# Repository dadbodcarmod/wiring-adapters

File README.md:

DadBodCarMod Wiring Adapters
============================

Wiring adapters for the various cars we modify.

While we sometimes do custom wiring, one of the goals of our projects is to
simplify these projects so the average "dad bod" can do these to their own cars.
These adapters are ones we've created to minimize the required wiring changes to
our stock-ish cars.

Corolla 2006 DBW Dash to ADU
----------------------------

This adapter is for connecting an ECU Masters Advanced Display Unit (ADU) to the
stock dash connector on a Toyota Corolla.  This will likely work on other models
that have a similar dash.  It's intended to be used with a car using the ECU
Masters EMU Black engine computer, so many of the stock light/functions aren't
connected (e.g. tachometer comes via CAN bus instead of stock pin).

 * For EMU Master Advanced Display Unit (ADU)
 * For use with ECU Master EMU Black (likely will work with EMU Classic)
 * For use on Toyota Corolla 2003 to 2006 (tested on 2003 and 2006)
 * For use on Drive-by-Wire (DBW) and non-DBW cars
 * For use on cars without Anti-lock Braking System (ABS); two or three changes
   required for ABS

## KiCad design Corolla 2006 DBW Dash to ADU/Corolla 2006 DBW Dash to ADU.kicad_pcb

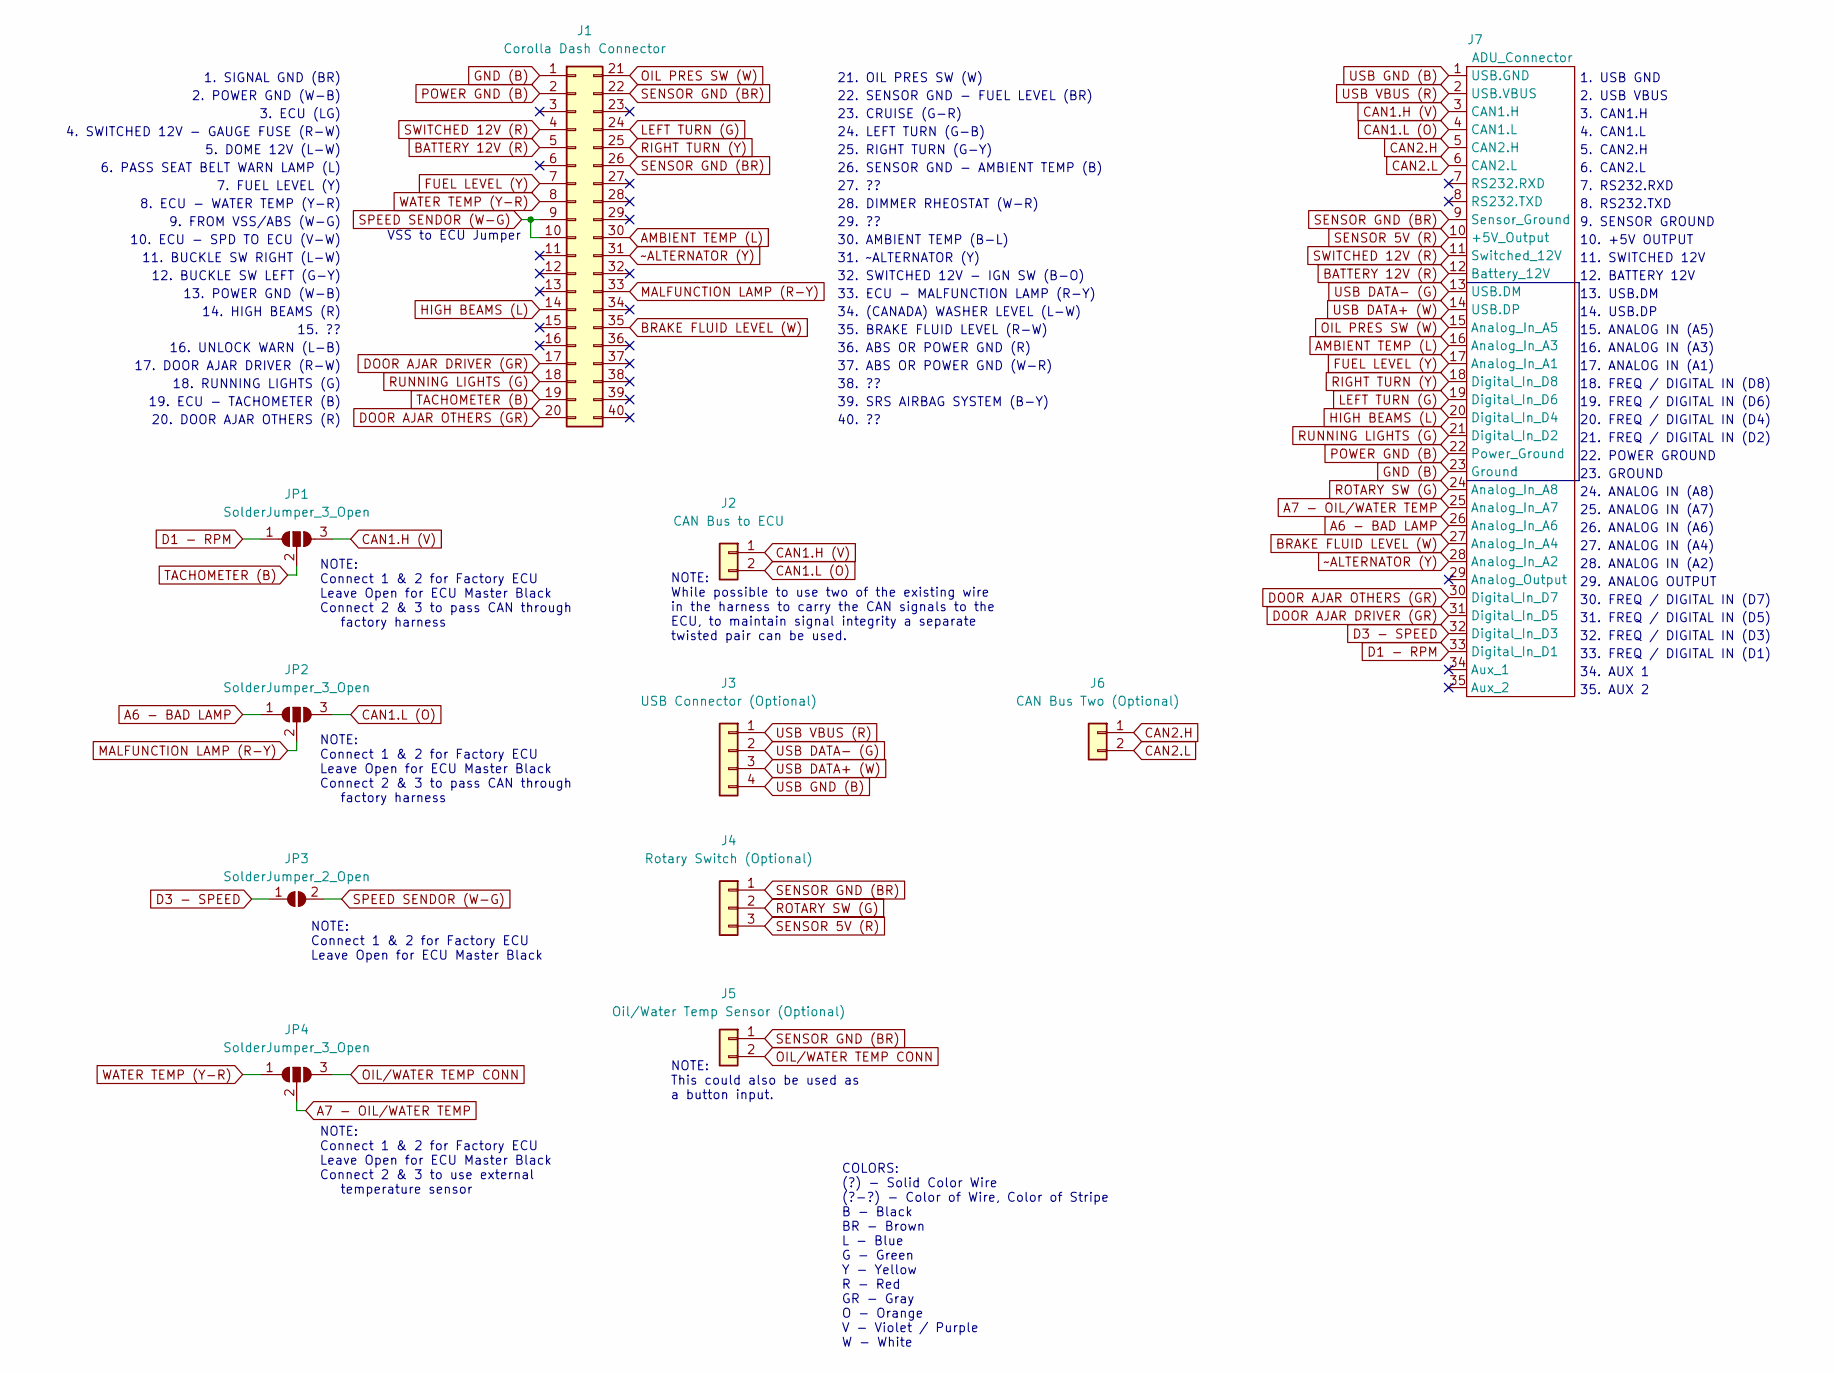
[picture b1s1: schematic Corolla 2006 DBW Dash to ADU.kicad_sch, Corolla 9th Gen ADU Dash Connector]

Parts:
J1: Corolla Dash Connector; 2006 Corolla Dash Connector
J2: CAN Bus to ECU; SolderWire-0.75sqmm_1x02_P4.8mm_D1.25mm_OD2.3mm_Relief
J3: USB Connector (Optional); SolderWire-0.25sqmm_1x04_P4.2mm_D0.65mm_OD1.7mm_Relief
J4: Rotary Switch (Optional); SolderWire-0.75sqmm_1x03_P4.8mm_D1.25mm_OD2.3mm_Relief
J5: Oil/Water Temp Sensor (Optional); SolderWire-0.75sqmm_1x02_P4.8mm_D1.25mm_OD2.3mm_Relief
J6: CAN Bus Two (Optional); SolderWire-0.75sqmm_1x02_P4.8mm_D1.25mm_OD2.3mm_Relief
J7: ADU_Connector; Wires for ADU Connector
JP1, JP2, JP4: SolderJumper_3_Open; SolderJumper-3_P1.3mm_Open_RoundedPad1.0x1.5mm_NumberLabels
JP3: SolderJumper_2_Open; SolderJumper-2_P1.3mm_Open_RoundedPad1.0x1.5mm

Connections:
A6 - BAD LAMP: J7.26 (Analog_In_A6), JP2.1 (A)
A7 - OIL/WATER TEMP: J7.25 (Analog_In_A7), JP4.2 (C)
AMBIENT TEMP (L): J1.30, J7.16 (Analog_In_A3)
BATTERY 12V (R): J1.5, J7.12 (Battery_12V)
BRAKE FLUID LEVEL (W): J1.35, J7.27 (Analog_In_A4)
CAN1.H (V): J2.1, J7.3 (CAN1.H), JP1.3 (B)
CAN1.L (O): J2.2, J7.4 (CAN1.L), JP2.3 (B)
CAN2.H: J6.1, J7.5 (CAN2.H)
CAN2.L: J6.2, J7.6 (CAN2.L)
D1 - RPM: J7.33 (Digital_In_D1), JP1.1 (A)
D3 - SPEED: J7.32 (Digital_In_D3), JP3.1 (A)
DOOR AJAR DRIVER (GR): J1.17, J7.31 (Digital_In_D5)
DOOR AJAR OTHERS (GR): J1.20, J7.30 (Digital_In_D7)
FUEL LEVEL (Y): J1.7, J7.17 (Analog_In_A1)
GND (B): J1.1, J7.23 (Ground)
HIGH BEAMS (L): J1.14, J7.20 (Digital_In_D4)
LEFT TURN (G): J1.24, J7.19 (Digital_In_D6)
MALFUNCTION LAMP (R-Y): J1.33, JP2.2 (C)
OIL PRES SW (W): J1.21, J7.15 (Analog_In_A5)
OIL/WATER TEMP CONN: J5.2, JP4.3 (B)
POWER GND (B): J1.2, J7.22 (Power_Ground)
RIGHT TURN (Y): J1.25, J7.18 (Digital_In_D8)
ROTARY SW (G): J4.2, J7.24 (Analog_In_A8)
RUNNING LIGHTS (G): J1.18, J7.21 (Digital_In_D2)
SENSOR 5V (R): J4.3, J7.10 (+5V_Output)
SENSOR GND (BR): J1.22, J1.26, J4.1, J5.1, J7.9 (Sensor_Ground)
SPEED SENDOR (W-G): J1.9, J1.10, JP3.2 (B)
SWITCHED 12V (R): J1.4, J7.11 (Switched_12V)
TACHOMETER (B): J1.19, JP1.2 (C)
USB DATA+ (W): J3.3, J7.14 (USB.DP)
USB DATA- (G): J3.2, J7.13 (USB.DM)
USB GND (B): J3.4, J7.1 (USB.GND)
USB VBUS (R): J3.1, J7.2 (USB.VBUS)
WATER TEMP (Y-R): J1.8, JP4.1 (A)
~ALTERNATOR (Y): J1.31, J7.28 (Analog_In_A2)

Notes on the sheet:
2. POWER GND (W-B)
38. ??
2. USB VBUS
14. USB.DP
34. (CANADA) WASHER LEVEL (L-W)
27. ANALOG IN (A4)
5. DOME 12V (L-W)
12. BUCKLE SW LEFT (G-Y)
8. RS232.TXD
4. SWITCHED 12V - GAUGE FUSE (R-W)
35. BRAKE FLUID LEVEL (R-W)
20. DOOR AJAR OTHERS (R)
33. ECU - MALFUNCTION LAMP (R-Y)
9. FROM VSS/ABS (W-G)
21. OIL PRES SW (W)
6. PASS SEAT BELT WARN LAMP (L)
20. FREQ / DIGITAL IN (D4)
3. ECU (LG)
18. RUNNING LIGHTS (G)
NOTE: Connect 1 & 2 for Factory ECU Leave Open for ECU Master Black Connect 2 & 3 to pass CAN through factory harness
31. ~ALTERNATOR (Y)
17. DOOR AJAR DRIVER (R-W)
3. CAN1.H
19. FREQ / DIGITAL IN (D6)
5. CAN2.H
18. FREQ / DIGITAL IN (D8)
33. FREQ / DIGITAL IN (D1)
4. CAN1.L
25. ANALOG IN (A7)
34. AUX 1
31. FREQ / DIGITAL IN (D5)
13. POWER GND (W-B)
COLORS: (?) - Solid Color Wire (?-?) - Color of Wire, Color of Stripe B - Black BR - Brown L - Blue G - Green Y - Yellow R - Red GR - Gray O - Orange V - Violet / Purple W - White
17. ANALOG IN (A1)
21. FREQ / DIGITAL IN (D2)
40. ??
23. CRUISE (G-R)
30. FREQ / DIGITAL IN (D7)
12. BATTERY 12V
NOTE: Connect 1 & 2 for Factory ECU Leave Open for ECU Master Black Connect 2 & 3 to use external temperature sensor

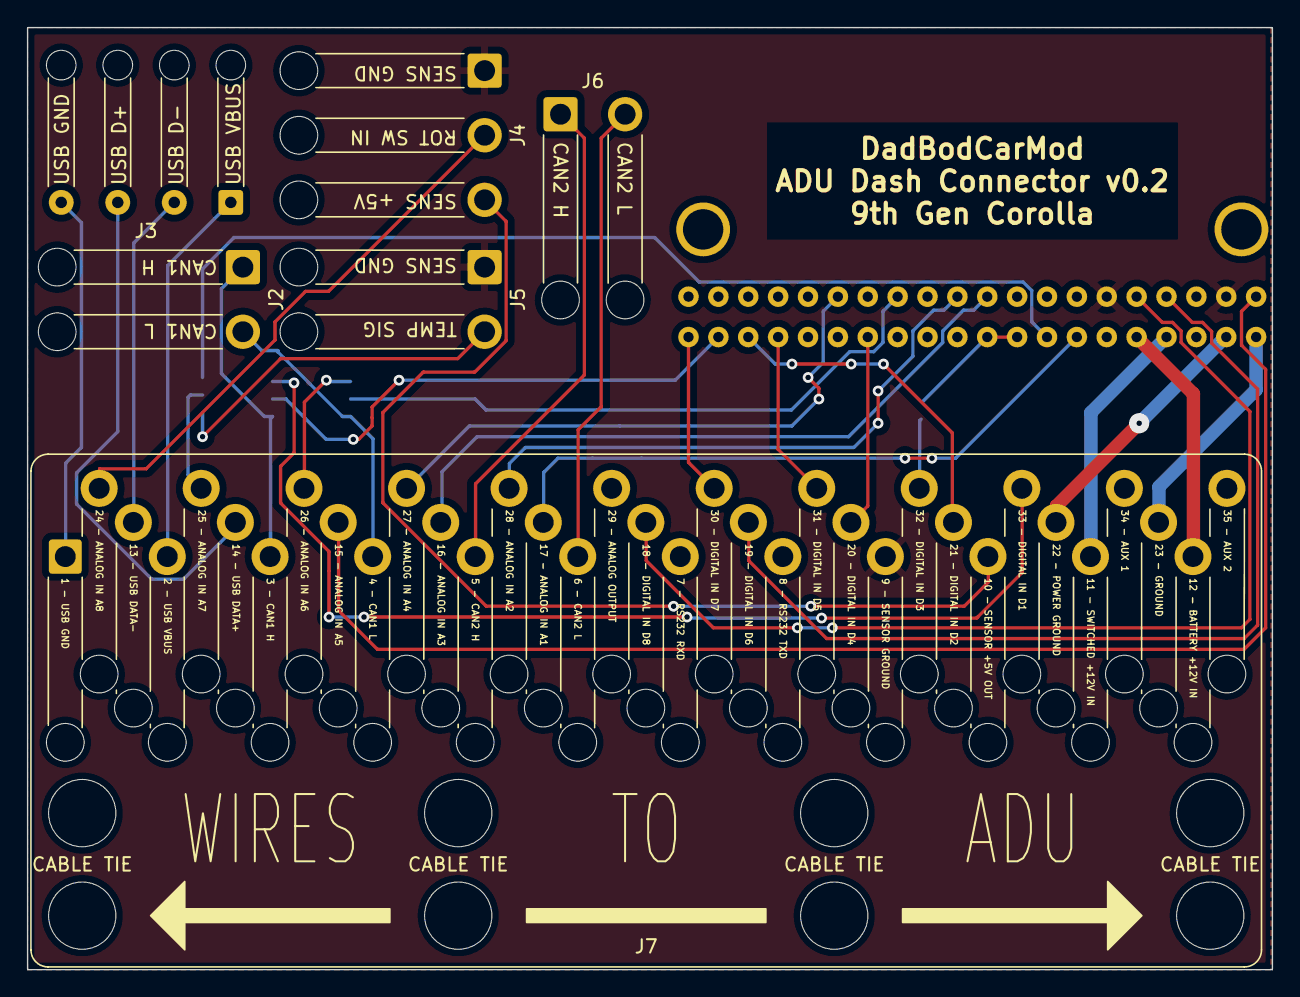
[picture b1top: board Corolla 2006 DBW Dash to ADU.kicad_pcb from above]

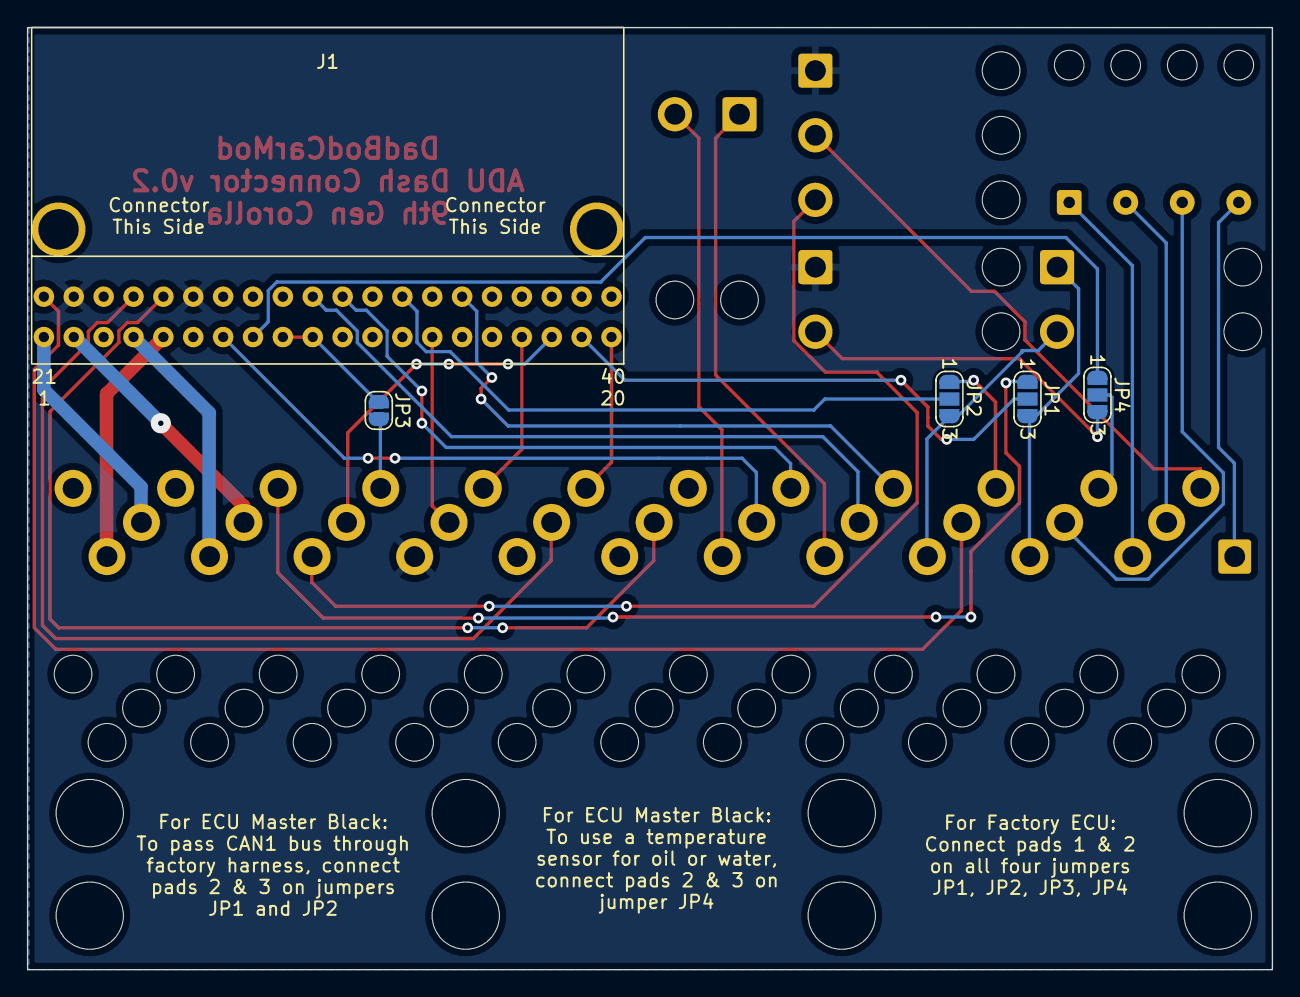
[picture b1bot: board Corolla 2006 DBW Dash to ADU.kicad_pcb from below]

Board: 2 copper layers, 92.5 x 70.0 mm, 11 parts (5 on the bottom side), 35 nets.

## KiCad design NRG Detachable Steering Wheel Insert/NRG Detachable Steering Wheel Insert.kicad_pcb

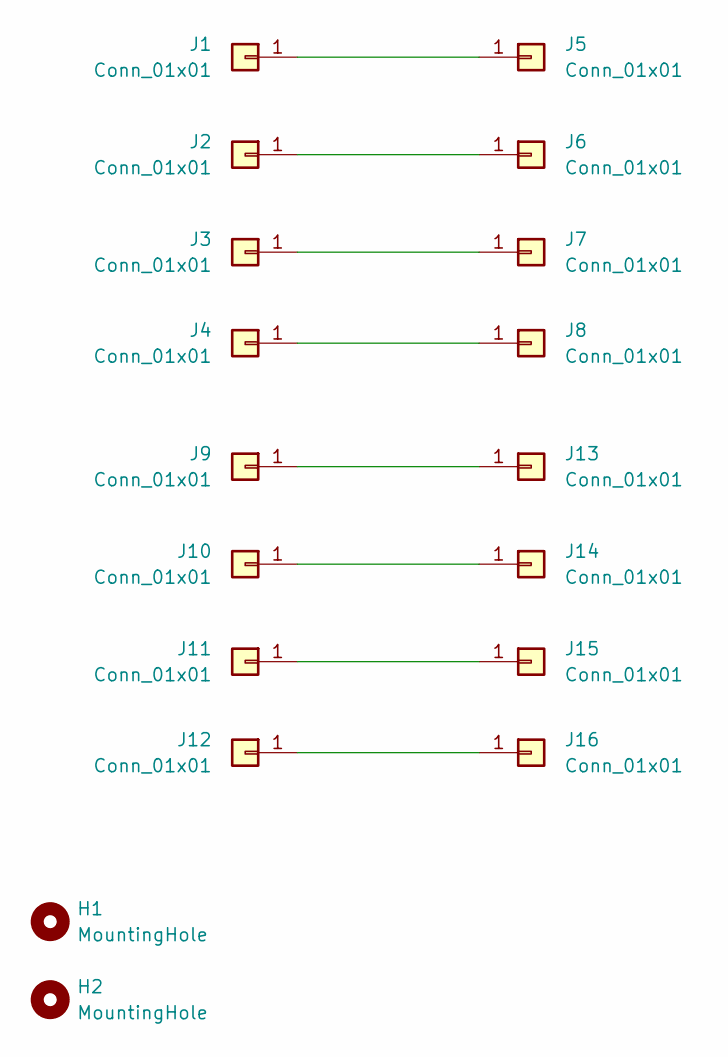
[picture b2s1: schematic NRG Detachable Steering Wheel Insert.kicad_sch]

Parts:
H1, H2: MountingHole; MountingHole_3.2mm_M3
J1, J2, J3, J4: Conn_01x01; SolderWire-1.5sqmm_1x01_D1.7mm_OD3mm; Part Num 0921-0-15-20-76-14-11-0
J5, J6, J7, J8, J9, J10, J11, J12, J13, J14, J15, J16: Conn_01x01; SolderWirePad_1x01_SMD_1x2mm

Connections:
unnamed: J1.1, J5.1
unnamed: J2.1, J6.1
unnamed: J3.1, J7.1
unnamed: J4.1, J8.1
unnamed: J10.1, J14.1
unnamed: J11.1, J15.1
unnamed: J12.1, J16.1
unnamed: J9.1, J13.1

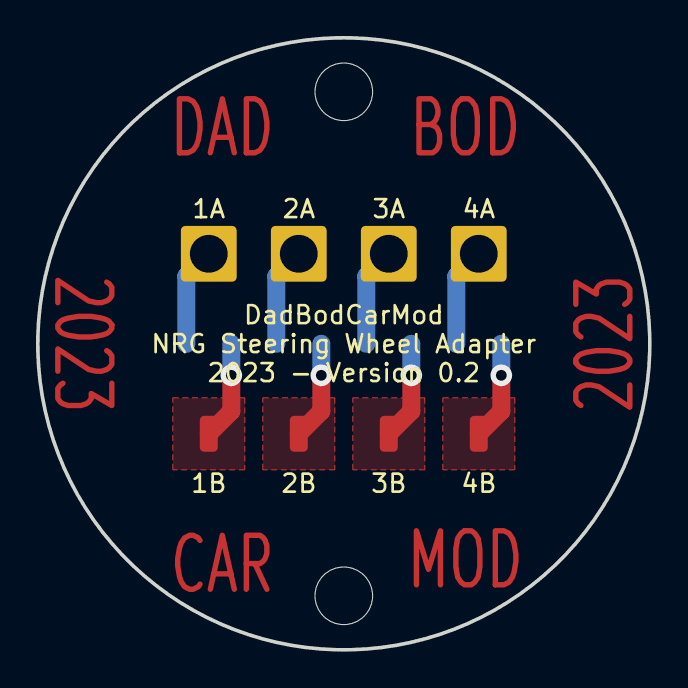
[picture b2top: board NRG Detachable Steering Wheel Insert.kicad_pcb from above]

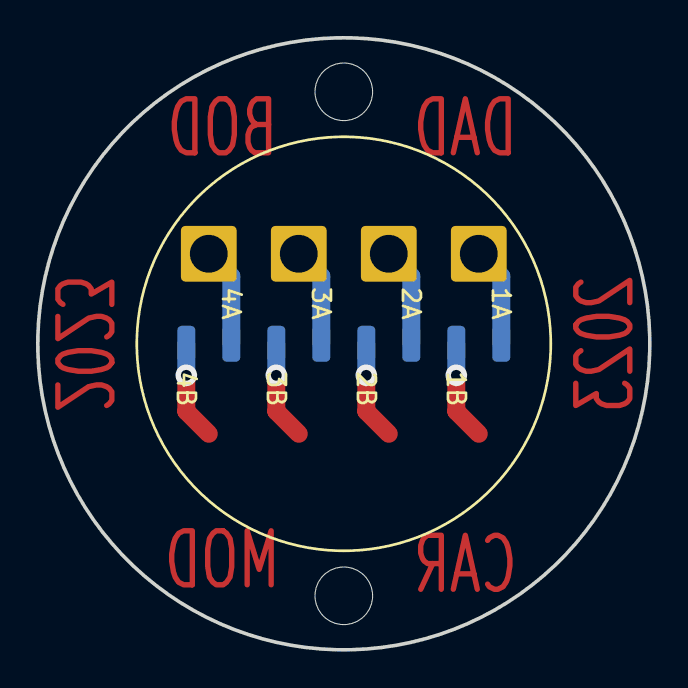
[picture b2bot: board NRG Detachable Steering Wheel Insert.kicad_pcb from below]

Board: 2 copper layers, 34.0 x 34.0 mm, 18 parts (8 on the bottom side), 8 nets.

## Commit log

2023-04-03 Adding the dash to ADU adapter.
2023-04-04 Added the rotary switch connector and fixed a few wires.
2023-04-04 Adding info to the README.md
2023-04-04 Adding a PDF version of the schematic for the Dash to ADU Adapter.
2023-04-04 Adding a submodule for kicad-libs.
2023-05-03 Adding updates and the 2006 DBW schematic.
2023-06-09 Adding the NRG Detachable Steering Wheel thingy.
2023-08-16 Updating the steering wheel insert to not touch the metal of the steering wheel.
2024-01-19 Now have a PCB to try.
2025-03-25 Commit whatever changes are in the repository.
2025-03-26 Commit new harness to EMU Black adapter.
2025-03-26 Updated the kicad-libs submodule.
2025-03-27 Added more nets
2025-03-27 Updated kicad-libs
2025-03-27 Adding the Lotus Elise dash to ADU adapter.
